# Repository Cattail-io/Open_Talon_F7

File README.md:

# Open Talon_F7
   Talon F7 20x20 Flight Controller full reverse and redesign - added baro BMP388.

   Kicad 5.x.x project of 6-layer PCB design.

   **The design wasn't checked in hardware, so you may use it at your own risk.**

 ## **Specs:**  
* MCU: STM32F722RET  
* On-board OSD: MAX7456  
* 5V 2A BEC MPQ4420  
* Pit mode switch  

  Preview:  
  ![alt-текст][board]

[board]: https://github.com/Cattail-io/Open_Talon_F7/blob/master/preview3d.png "3D View"

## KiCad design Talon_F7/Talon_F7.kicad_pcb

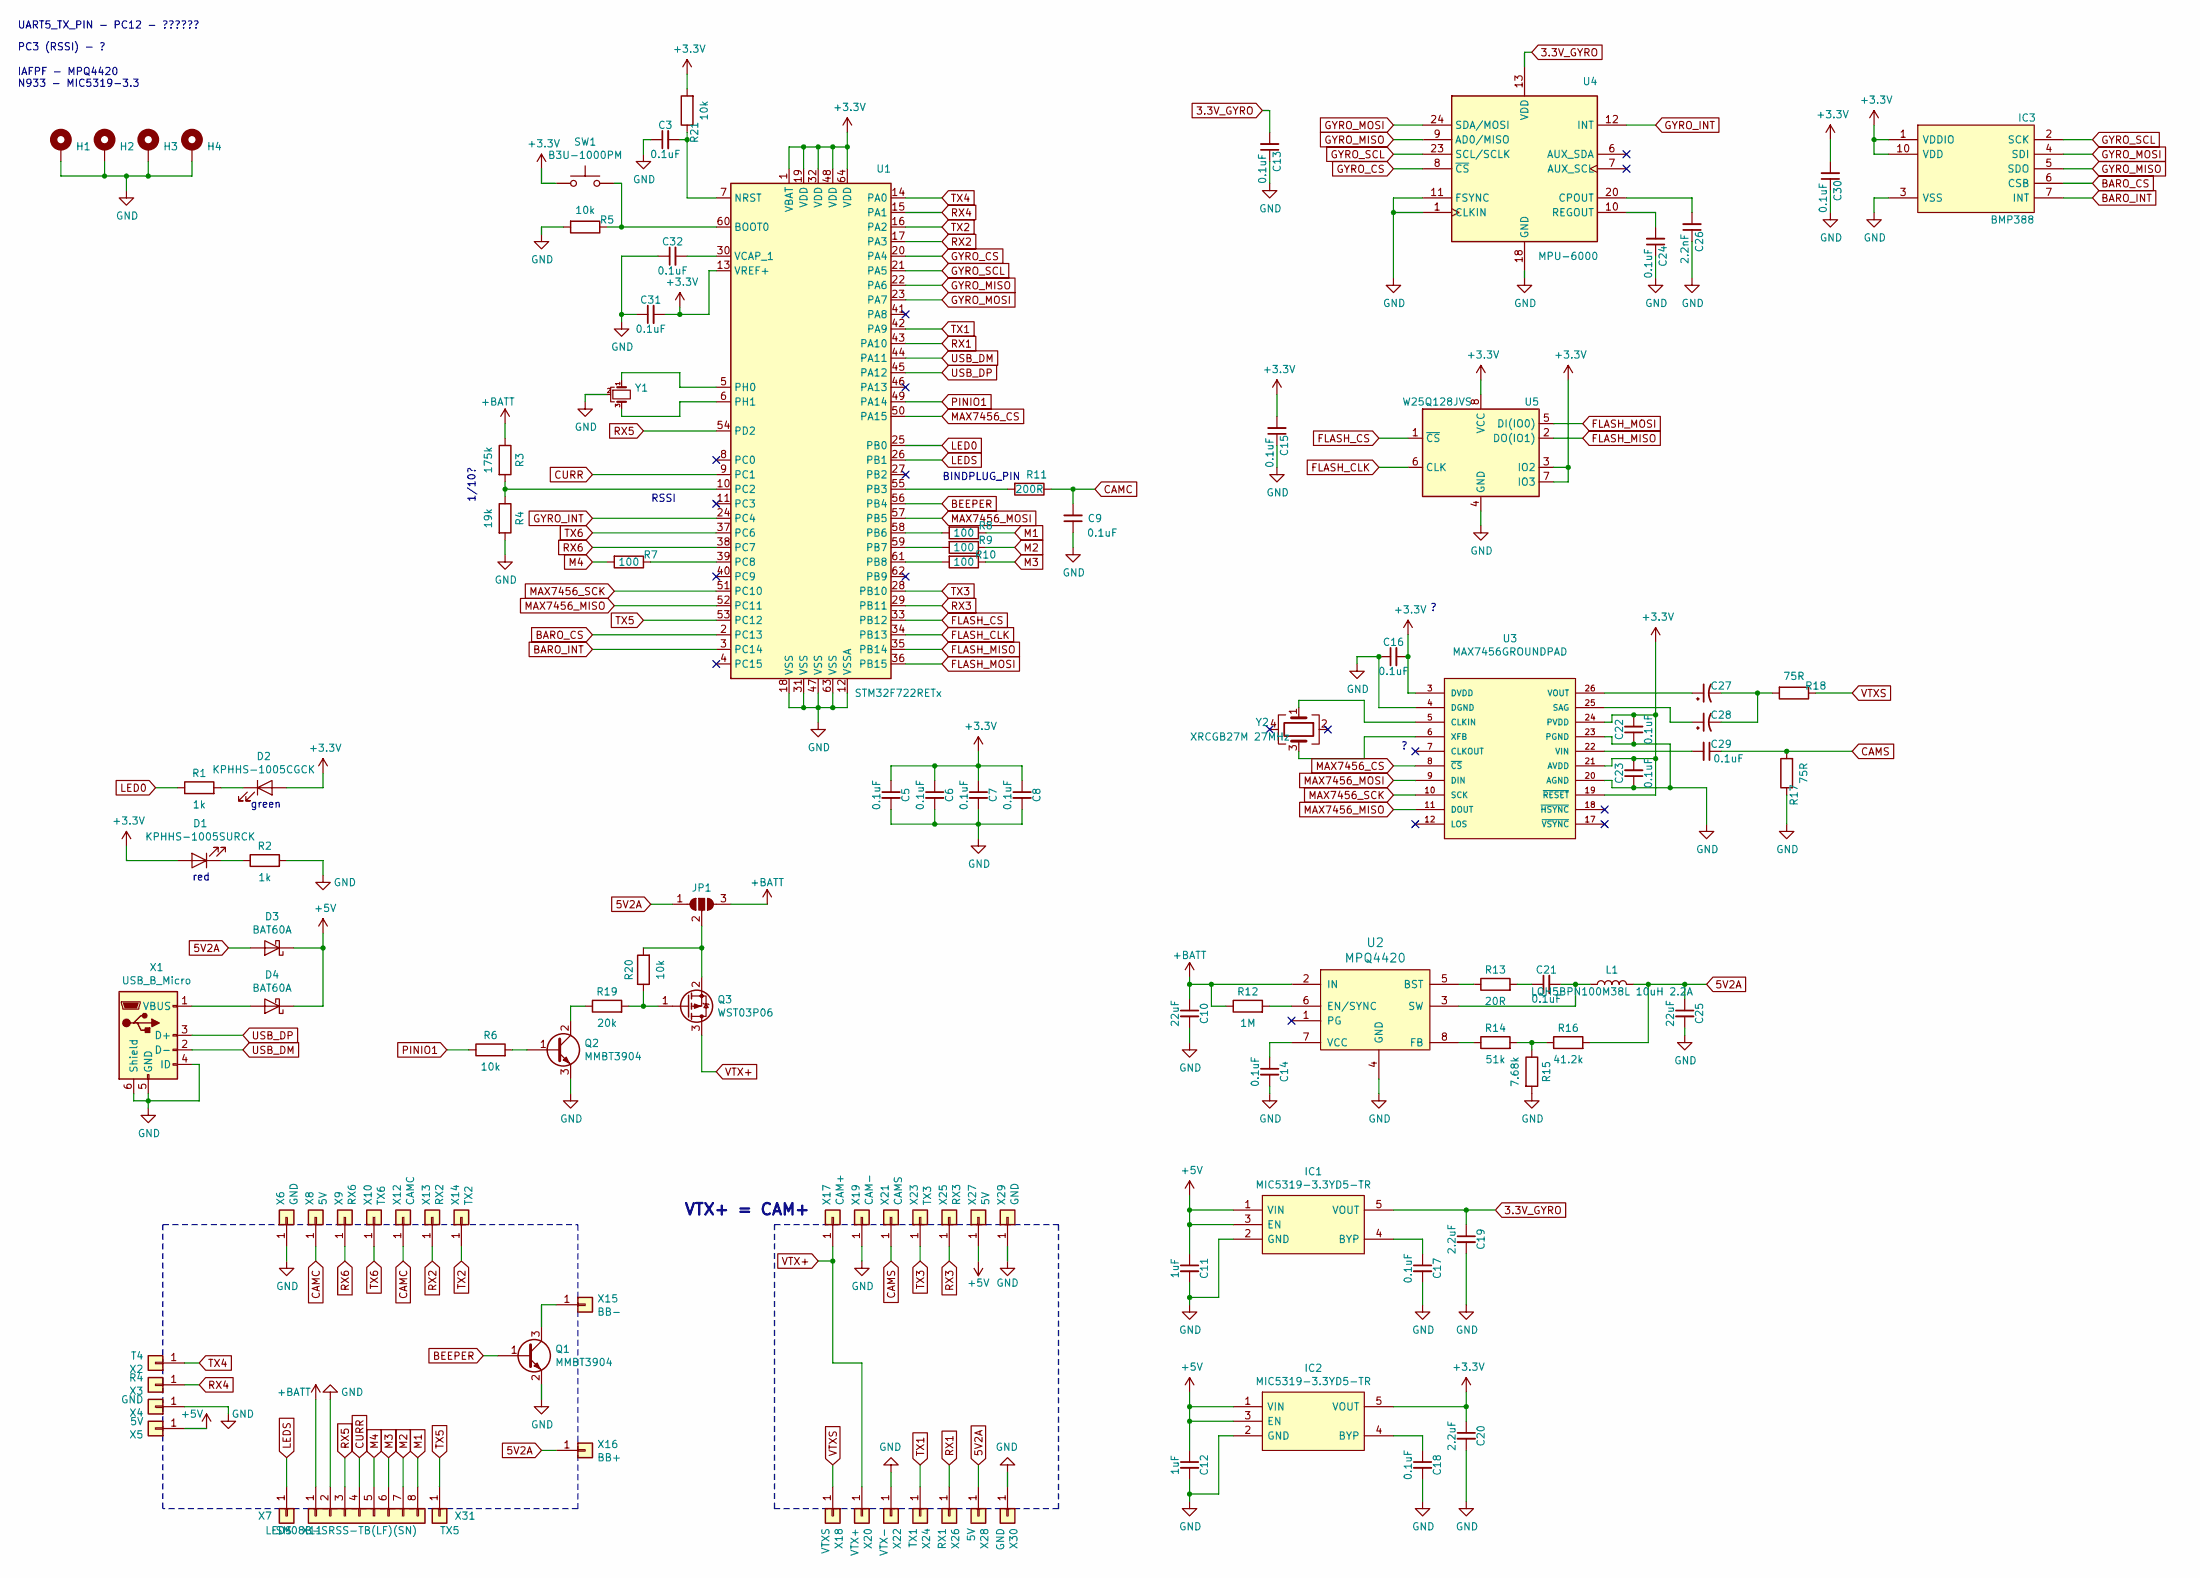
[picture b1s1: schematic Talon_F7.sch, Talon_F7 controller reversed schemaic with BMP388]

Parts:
C3, C5, C6, C7, C8, C9, C13, C14, C15, C16, C17, C18, C21, C22, C23, C24, C29, C30, C31, C32: 0.1uF; C_0402_1005Metric
C10, C25: 22uF; C_0402_1005Metric
C11, C12: 1uF; C_0402_1005Metric
C19, C20: 2.2uF; C_0402_1005Metric
C26: 2.2nF; C_0402_1005Metric
C27, C28: 22uF; C_0603_1608Metric
D1: KPHHS-1005SURCK; LED_0402_1005Metric
D2: KPHHS-1005CGCK; LED_0402_1005Metric
D3, D4: BAT60A; D_SOD-323
H1, H2, H3, H4: MountingHole_Pad; PAD_2.7mm_D5.0mm
IC1: MIC5319-3.3YD5-TR; SOT-23-5
IC2: MIC5319-3.3YD5-TR; SOT-23-5; Manufacturer_Part_Number MIC5319-3.3YD5-TR; Mouser Part Number 998-MIC5319-3.3YD5TR
IC3: BMP388
JP1: SolderJumper_3_Open; SolderJumper-3_P1.3mm_Open_RoundedPad1.0x1.5mm_NumberLabels
L1: LQH5BPN100M38L 10uH 2.2A; L_Taiyo-Yuden_NR-50xx
Q1, Q2: MMBT3904; SOT-23
Q3: WST03P06; SOT-23
R1, R2: 1k; R_0402_1005Metric
R3: 175k; R_0402_1005Metric
R4: 19k; R_0402_1005Metric
R5, R6, R20, R21: 10k; R_0402_1005Metric
R7, R8, R9, R10: 100; R_0402_1005Metric
R11: 200R; R_0402_1005Metric
R12: 1M; R_0402_1005Metric
R13: 20R; R_0402_1005Metric
R14: 51k; R_0402_1005Metric
R15: 7.68k; R_0402_1005Metric
R16: 41.2k; R_0402_1005Metric
R17, R18: 75R; R_0402_1005Metric
R19: 20k; R_0402_1005Metric
SW1: B3U-1000PM; SW_SPST_B3U-1000P
U1: STM32F722RETx; LQFP-64_10x10mm_P0.5mm
U2: MPQ4420; TSOT32-8
U3: MAX7456GROUNDPAD; TSSOP28-GROUNDPAD
U4: MPU-6000; InvenSense_QFN-24_4x4mm_P0.5mm
U5: W25Q128JVS; SOIC-8_5.23x5.23mm_P1.27mm
X1: USB_B_Micro; USB_Micro-B_Molex_47346-0001
X2: T4; Pad_SMD_1.5x2.0mm
X3: R4; Pad_SMD_1.5x2.0mm
X4, X6, X29, X30: GND; Pad_SMD_1.5x2.0mm
X5, X8, X27, X28: 5V; Pad_SMD_1.5x2.0mm
X7: LEDS; Pad_SMD_1.5x2.0mm
X9: RX6; Pad_SMD_1.5x2.0mm
X10: TX6; Pad_SMD_1.5x2.0mm
X11: SM08B-SRSS-TB(LF)(SN); JST_SH_SM08B-SRSS-TB_1x08-1MP_P1.00mm_Horizontal
X12: CAMC; Pad_SMD_1.5x2.0mm
X13: RX2; Pad_SMD_1.5x2.0mm
X14: TX2; Pad_SMD_1.5x2.0mm
X15: BB-; Pad_SMD_1.5x2.0mm
X16: BB+; Pad_SMD_1.5x2.0mm
X17: CAM+; Pad_SMD_1.5x2.0mm
X18: VTXS; Pad_SMD_1.5x2.0mm
X19: CAM-; Pad_SMD_1.5x2.0mm
X20: VTX+; Pad_SMD_1.5x2.0mm
X21: CAMS; Pad_SMD_1.5x2.0mm
X22: VTX-; Pad_SMD_1.5x2.0mm
X23: TX3; Pad_SMD_1.5x2.0mm
X24: TX1; Pad_SMD_1.5x2.0mm
X25: RX3; Pad_SMD_1.5x2.0mm
X26: RX1; Pad_SMD_1.5x2.0mm
X31: TX5; Pad_SMD_1.5x2.0mm
Y1: CSTNE8M00G55Z000R0 8MHz; Resonator_SMD_muRata_CSTxExxV-3Pin_3.0x1.1mm
Y2: XRCGB27M 27MHz; Crystal_SMD_2016-4Pin_2.0x1.6mm

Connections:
3.3V_GYRO: C13.2, C19.1, IC1.5 (VOUT), U4.13 (VDD)
5V2A: C25.1, D3.2 (A), JP1.1 (A), L1.2, R16.2, X16.1, X28.1
+3V3: C5.1, C6.1, C7.1, C8.1, C15.2, C16.2, C20.1, C22.2, C23.2, C30.2, C31.2, D1.2 (A), D2.2 (A), IC2.5 (VOUT), IC3.1 (VDDIO), IC3.10 (VDD), R21.2, SW1.1, U1.1 (VBAT), U1.13 (VREF+), U1.19 (VDD), U1.32 (VDD), U1.48 (VDD), U1.64 (VDD), U3.3 (DVDD), U3.19 (~RESET), U3.21 (AVDD), U3.24 (PVDD), U5.3 (IO2), U5.7 (IO3), U5.8 (VCC)
+5V: C11.1, C12.1, D3.1 (K), D4.1 (K), IC1.1 (VIN), IC1.3 (EN), IC2.1 (VIN), IC2.3 (EN), X5.1, X27.1
+BATT: C10.1, JP1.3 (B), R3.1, R12.1, U2.2 (IN), X11.1
BARO_CS: IC3.6 (CSB), U1.2 (PC13)
BARO_INT: IC3.7 (INT), U1.3 (PC14)
BEEPER: Q1.1 (B), U1.56 (PB4)
CAMC: C9.2, R11.1, X8.1, X12.1
CAMS: C29.1, R17.2, X21.1
CURR: U1.9 (PC1), X11.4
FLASH_CLK: U1.34 (PB13), U5.6 (CLK)
FLASH_CS: U1.33 (PB12), U5.1 (~CS)
FLASH_MISO: U1.35 (PB14), U5.2 (DO(IO1))
FLASH_MOSI: U1.36 (PB15), U5.5 (DI(IO0))
GND: C3.1, C5.2, C6.2, C7.2, C8.2, C9.1, C10.2, C11.2, C12.2, C13.1, C14.2, C15.1, C16.1, C17.2, C18.2, C19.2, C20.2, C22.1, C23.1, C24.1, C25.2, C26.1, C30.1, C31.1, C32.1, H1.1, H2.1, H3.1, H4.1, IC1.2 (GND), IC2.2 (GND), IC3.3 (VSS), IC3.8 (VSS), IC3.9 (VSS), Q1.2 (E), Q2.3 (E), R2.2, R4.2, R5.2, R15.2, R17.1, U1.12 (VSSA), U1.18 (VSS), U1.31 (VSS), U1.47 (VSS), U1.63 (VSS), U2.4 (GND), U3.4 (DGND), U3.20 (AGND), U3.23 (PGND), U4.1 (CLKIN), U4.11 (FSYNC), U4.18 (GND), U5.4 (GND), X1.4 (ID), X1.5 (GND), X1.6 (Shield), X4.1, X6.1, X11.2, X19.1, X22.1, X29.1, X30.1, Y1.2
GYRO_CS: U1.20 (PA4), U4.8 (~CS)
GYRO_INT: U1.24 (PC4), U4.12 (INT)
GYRO_MISO: IC3.5 (SDO), U1.22 (PA6), U4.9 (AD0/MISO)
GYRO_MOSI: IC3.4 (SDI), U1.23 (PA7), U4.24 (SDA/MOSI)
GYRO_SCL: IC3.2 (SCK), U1.21 (PA5), U4.23 (SCL/SCLK)
LED0: R1.1, U1.25 (PB0)
LEDS: U1.26 (PB1), X7.1
M1: R8.1, X11.8
M2: R9.1, X11.7
M3: R10.1, X11.6
M4: R7.2, X11.5
MAX7456_CS: U1.50 (PA15), U3.8 (~CS)
MAX7456_MISO: U1.52 (PC11), U3.11 (DOUT)
MAX7456_MOSI: U1.57 (PB5), U3.9 (DIN)
MAX7456_SCK: U1.51 (PC10), U3.10 (SCK)
unnamed: C3.2, R21.1, U1.7 (NRST)
unnamed: C14.1, U2.7 (VCC)
unnamed: C17.1, IC1.4 (BYP)
unnamed: C18.1, IC2.4 (BYP)
unnamed: C21.1, R13.2
unnamed: C21.2, L1.1, U2.3 (SW)
unnamed: C24.2, U4.10 (REGOUT)
unnamed: C26.2, U4.20 (CPOUT)
unnamed: C27.1, U3.26 (VOUT)
unnamed: C27.2, C28.2, R18.2
unnamed: C28.1, U3.25 (SAG)
unnamed: C29.2, U3.22 (VIN)
unnamed: C32.2, U1.30 (VCAP_1)
unnamed: D1.1 (K), R2.1
unnamed: D2.1 (K), R1.2
unnamed: D4.2 (A), X1.1 (VBUS)
unnamed: JP1.2 (C), Q3.2 (S), R20.2
unnamed: Q1.3 (C), X15.1
unnamed: Q2.1 (B), R6.2
unnamed: Q2.2 (C), R19.1
unnamed: Q3.1 (G), R19.2, R20.1
unnamed: R3.2, R4.1, U1.10 (PC2)
unnamed: R5.1, SW1.2, U1.60 (BOOT0)
unnamed: R7.1, U1.39 (PC8)
unnamed: R8.2, U1.58 (PB6)
unnamed: R9.2, U1.59 (PB7)
unnamed: R10.2, U1.61 (PB8)
unnamed: R11.2, U1.55 (PB3)
unnamed: R12.2, U2.6 (EN/SYNC)
unnamed: R13.1, U2.5 (BST)
unnamed: R14.1, U2.8 (FB)
unnamed: R14.2, R15.1, R16.1
unnamed: U1.5 (PH0), Y1.1
unnamed: U1.6 (PH1), Y1.3
unnamed: U3.5 (CLKIN), Y2.1
unnamed: U3.6 (XFB), Y2.3
PINIO1: R6.1, U1.49 (PA14)
RX1: U1.43 (PA10), X26.1
RX2: U1.17 (PA3), X13.1
RX3: U1.29 (PB11), X25.1
RX4: U1.15 (PA1), X3.1
RX5: U1.54 (PD2), X11.3
RX6: U1.38 (PC7), X9.1
TX1: U1.42 (PA9), X24.1
TX2: U1.16 (PA2), X14.1; also elsewhere on the board
TX3: U1.28 (PB10), X23.1
TX4: U1.14 (PA0), X2.1
TX5: U1.53 (PC12), X31.1
TX6: U1.37 (PC6), X10.1
USB_DM: U1.44 (PA11), X1.2 (D-)
USB_DP: U1.45 (PA12), X1.3 (D+)
VTX+: Q3.3 (D), X17.1, X20.1
VTXS: R18.1, X18.1

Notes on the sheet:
PC3 (RSSI) - ?
IAFPF - MPQ4420 N933 - MIC5319-3.3
1/10?
VTX+ = CAM+
UART5_TX_PIN - PC12 - ??????
RSSI
BINDPLUG_PIN
red
green

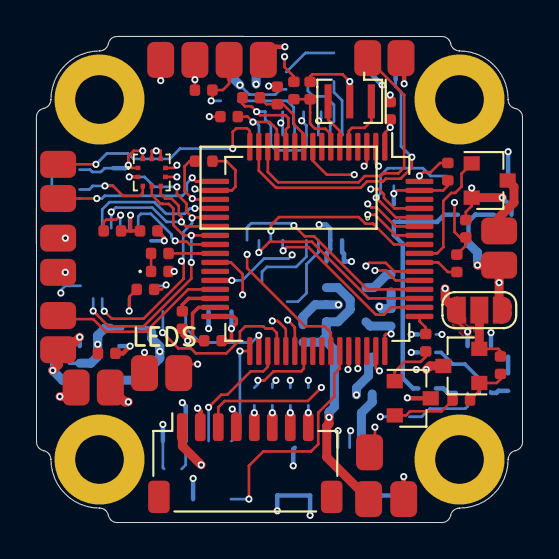
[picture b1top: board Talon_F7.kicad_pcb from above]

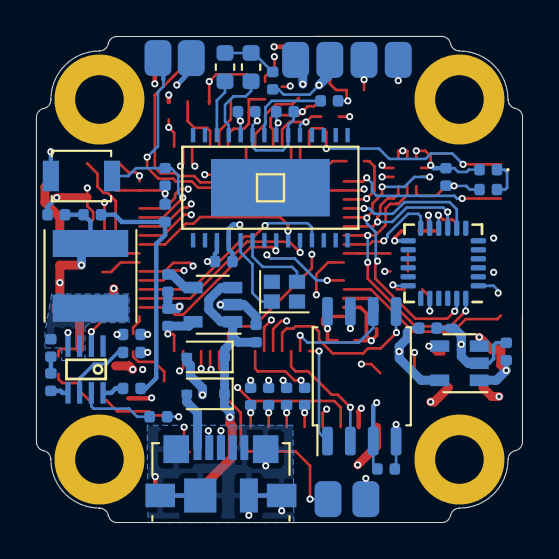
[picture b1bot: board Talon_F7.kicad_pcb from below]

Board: 6 copper layers, 27.0 x 27.0 mm, 105 parts (50 on the bottom side), 84 nets.

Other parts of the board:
TX2: TX2; Pad_SMD_1.5x2.0mm

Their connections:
TX2: TX2.1; also elsewhere on the board
